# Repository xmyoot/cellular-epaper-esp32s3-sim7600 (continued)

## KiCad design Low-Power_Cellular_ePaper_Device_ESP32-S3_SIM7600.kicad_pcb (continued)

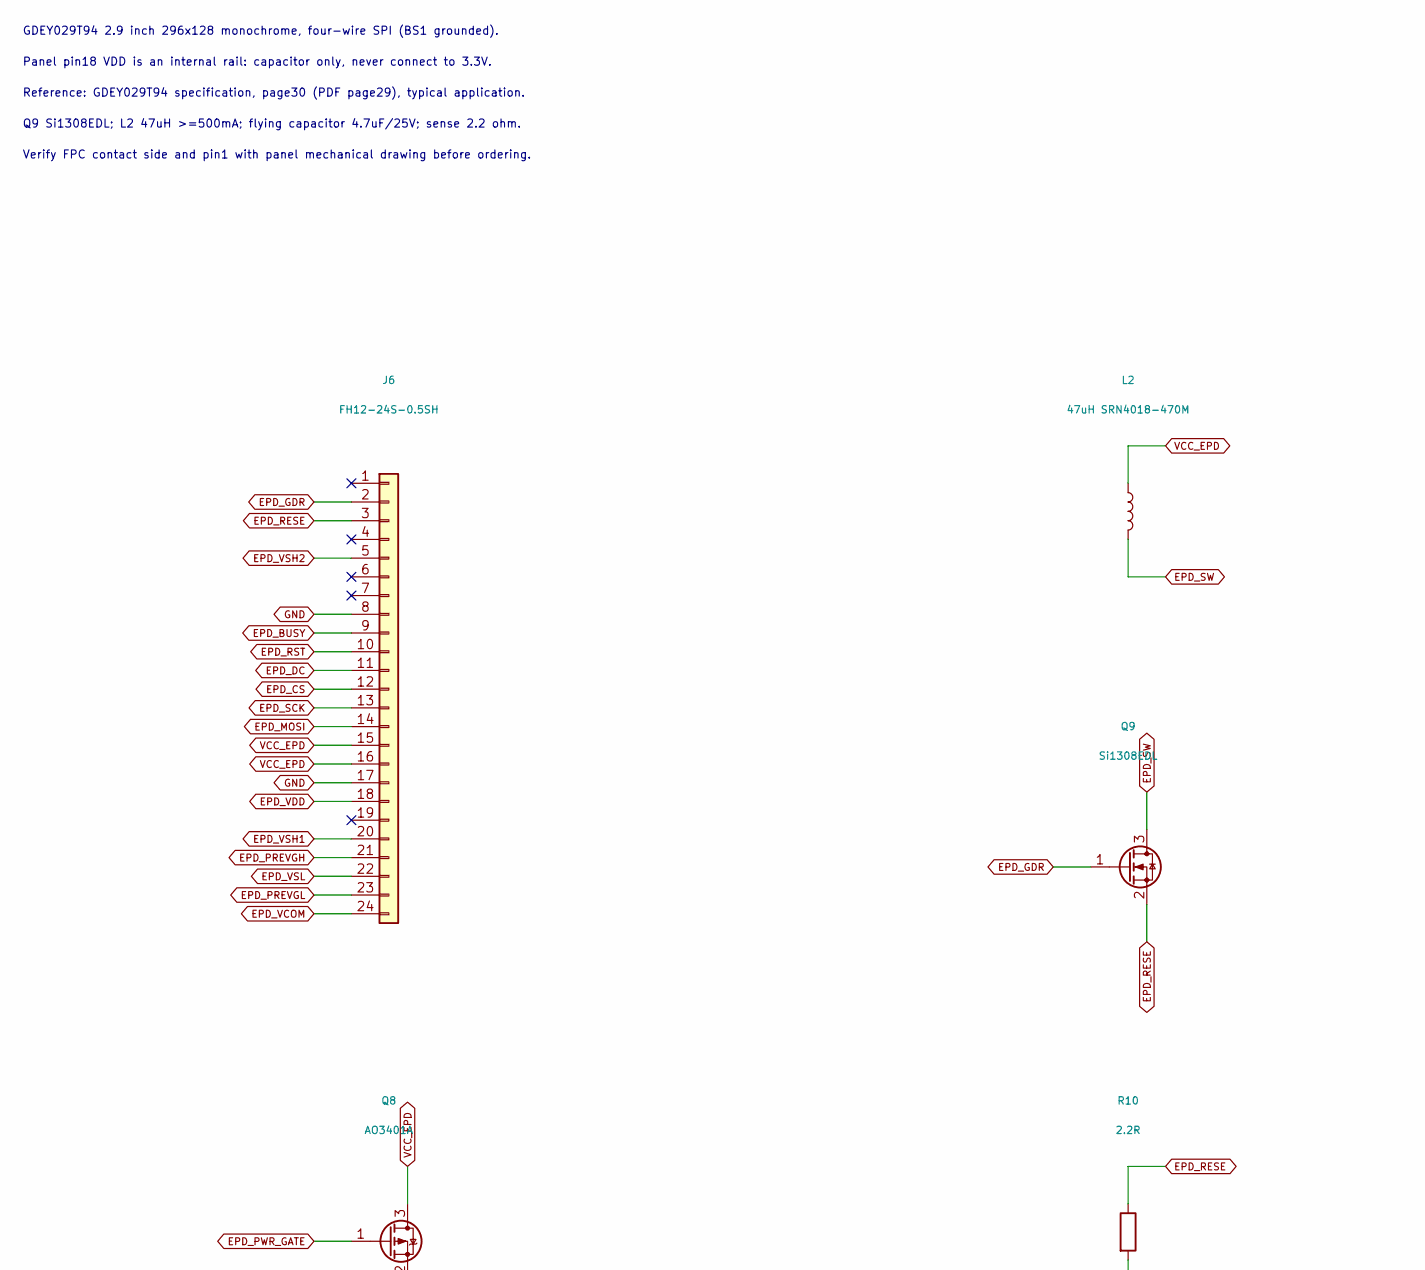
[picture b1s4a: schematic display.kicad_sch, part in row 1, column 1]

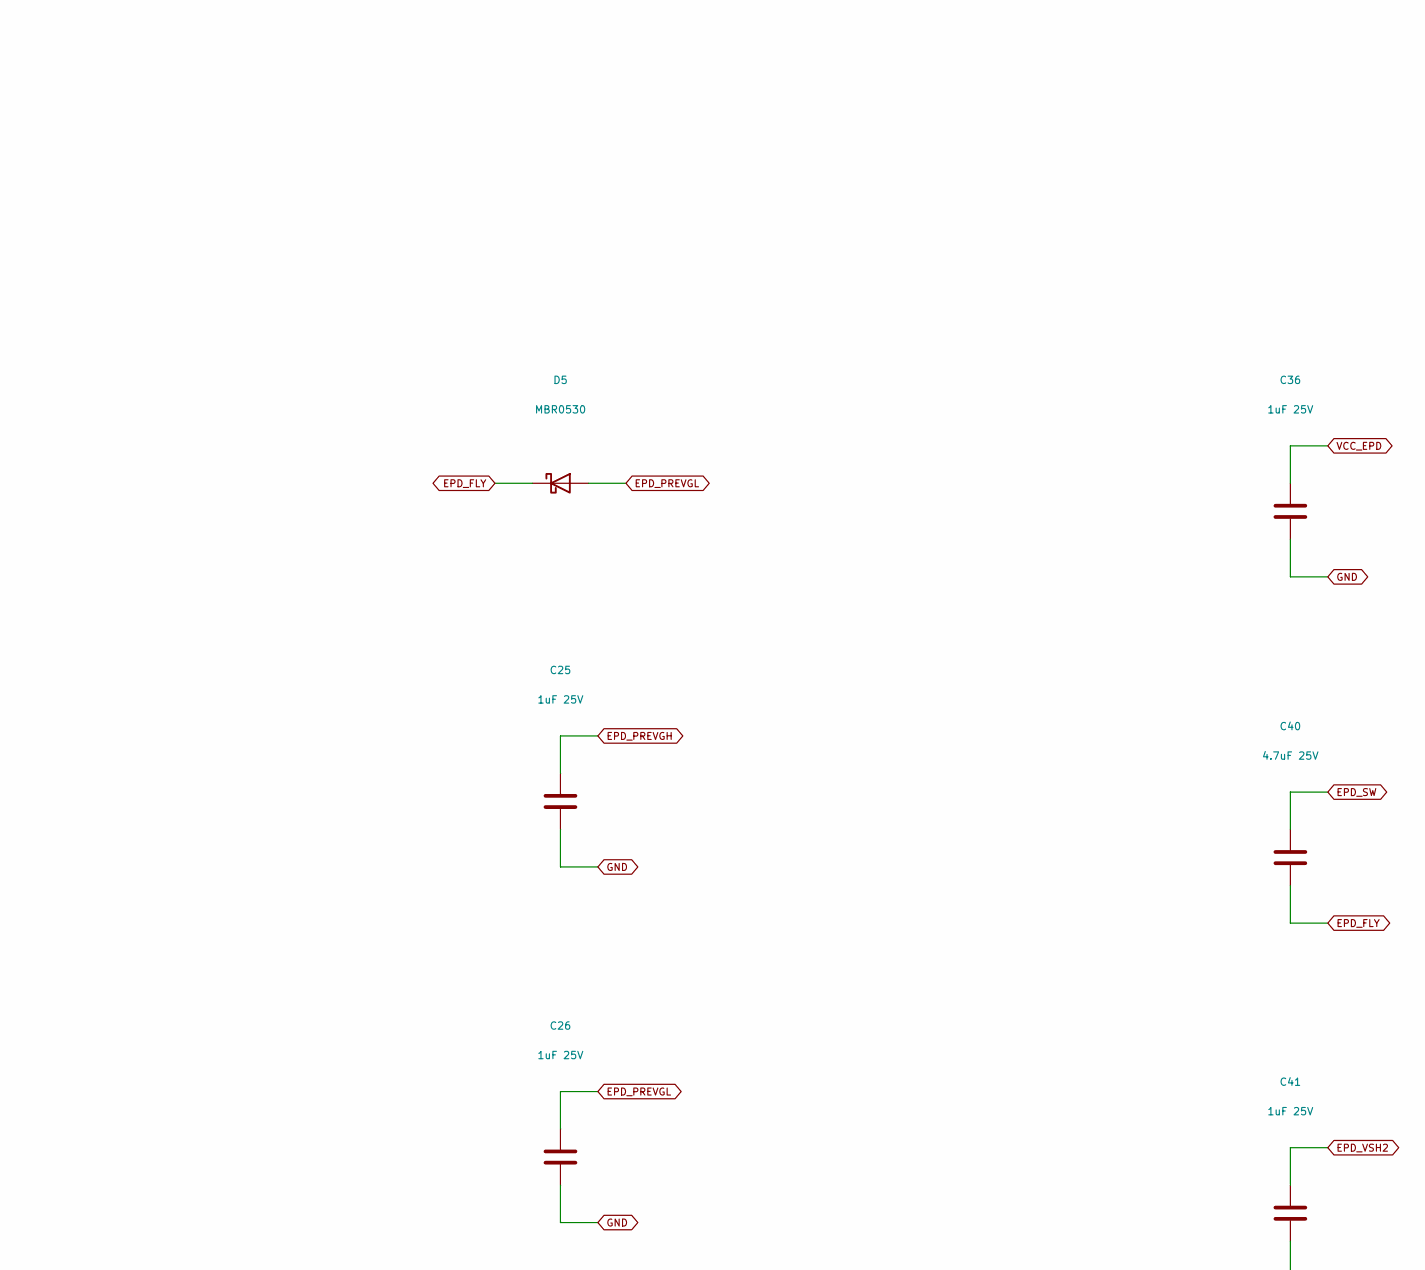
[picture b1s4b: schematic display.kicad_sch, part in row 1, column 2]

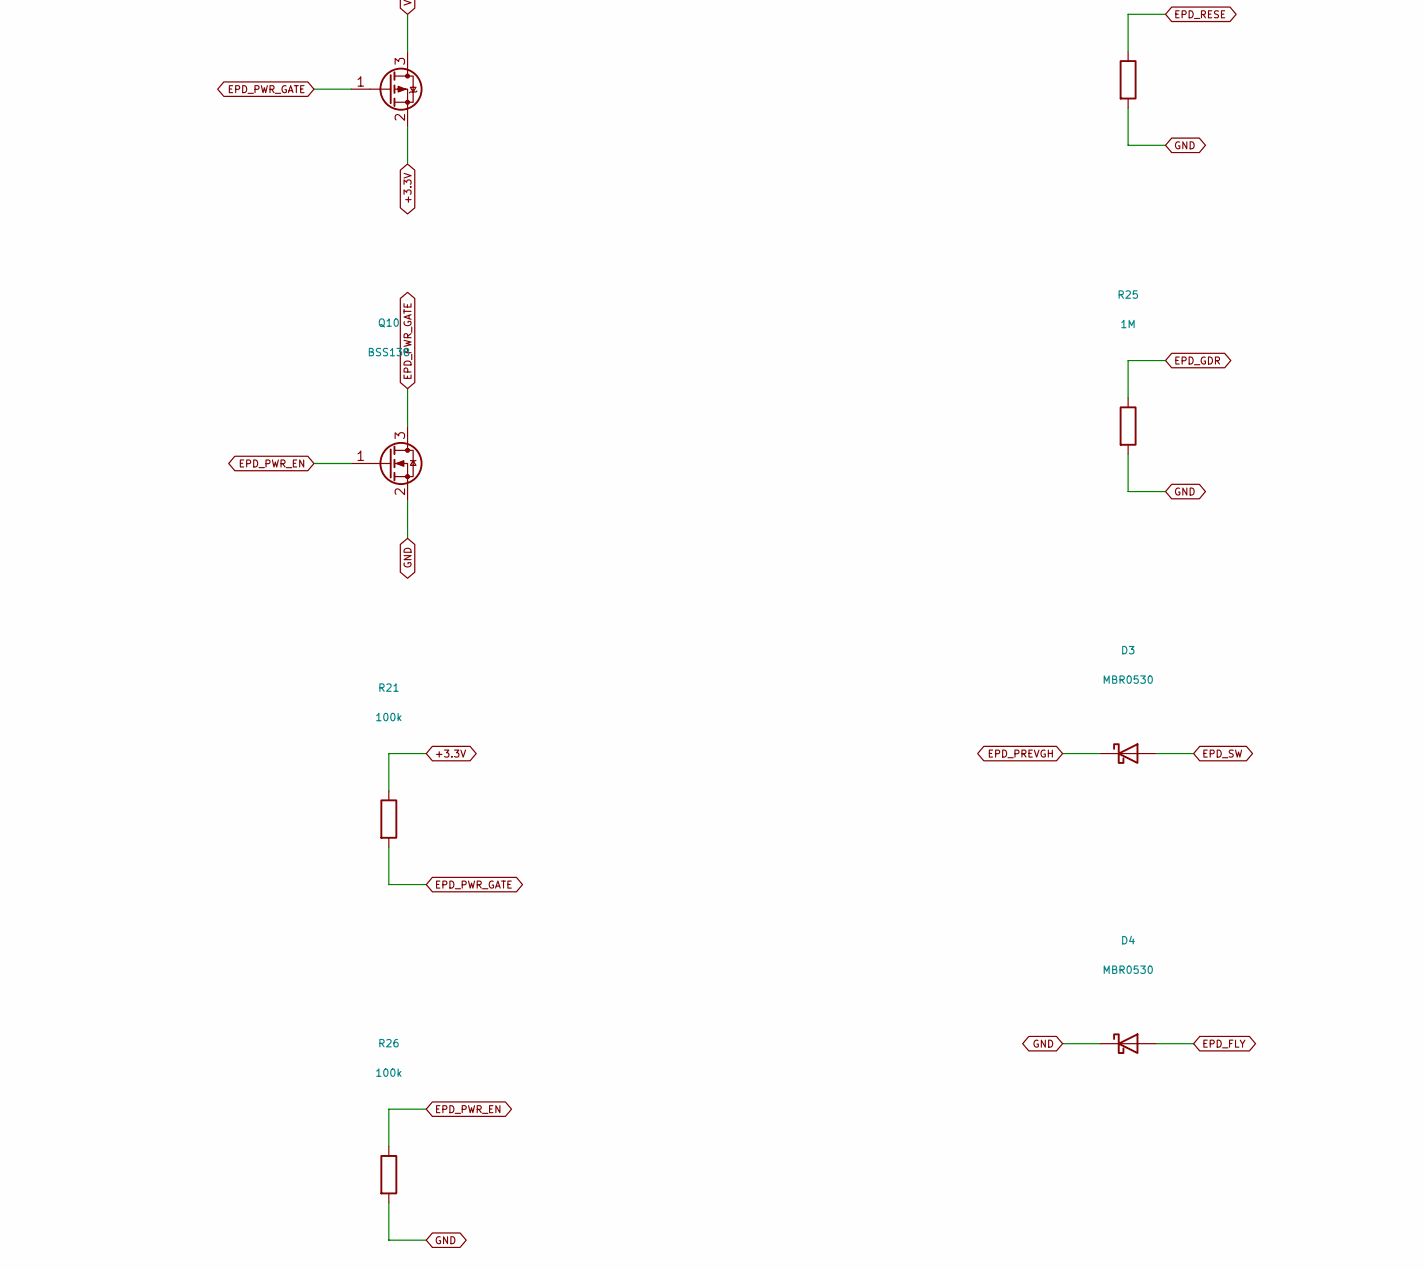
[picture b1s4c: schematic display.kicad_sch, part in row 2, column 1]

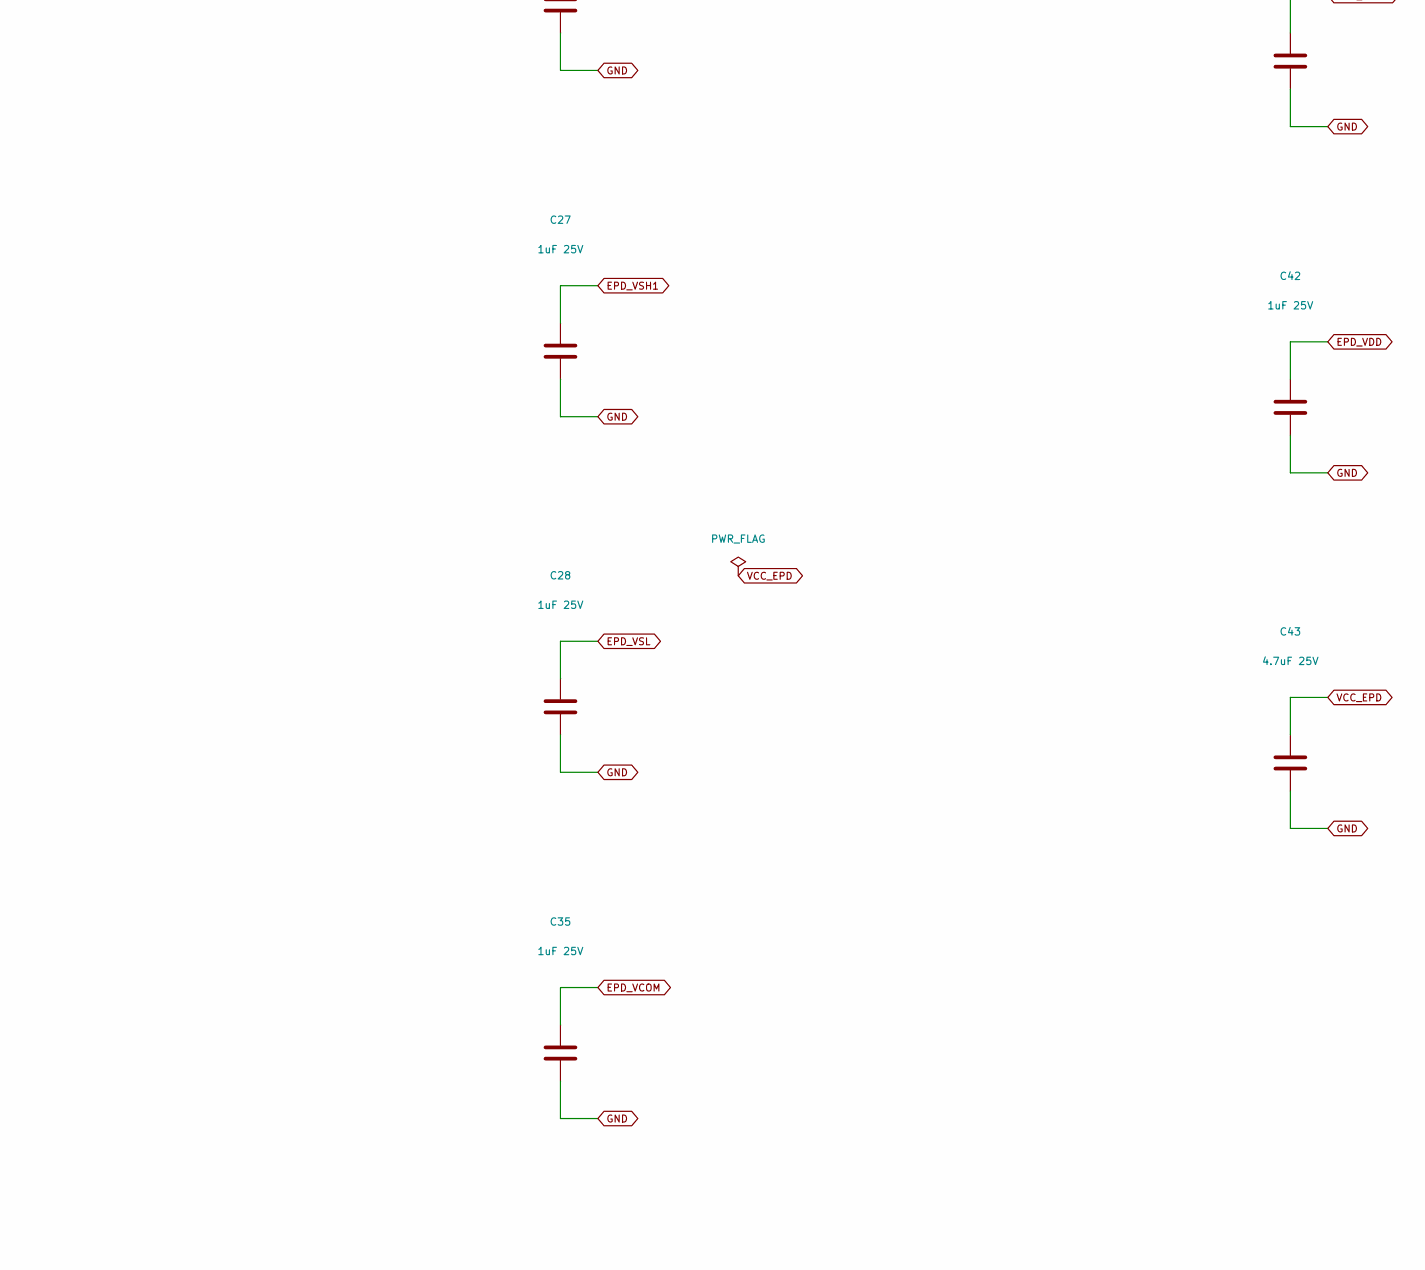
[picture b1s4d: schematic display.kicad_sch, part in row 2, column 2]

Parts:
C25, C26, C27, C28, C35, C41, C42: 1uF 25V; C_0805_2012Metric
C36: 1uF 25V; C_0603_1608Metric
C40, C43: 4.7uF 25V; C_0805_2012Metric
D3, D4, D5: MBR0530; D_SOD-123
J6: FH12-24S-0.5SH; Hirose_FH12-24S-0.5SH_1x24-1MP_P0.50mm_Horizontal
L2: 47uH SRN4018-470M; L_Bourns-SRN4018
Q8: AO3401A; SOT-23
Q9: Si1308EDL; SOT-323_SC-70
Q10: BSS138; SOT-23
R10: 2.2R; R_0805_2012Metric
R21, R26: 100k; R_0603_1608Metric
R25: 1M; R_0603_1608Metric

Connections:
+3.3V: Q8.2 (S), R21.1; also elsewhere on the board
EPD_BUSY: J6.9; also elsewhere on the board
EPD_CS: J6.12; also elsewhere on the board
EPD_DC: J6.11; also elsewhere on the board
EPD_FLY: C40.2, D4.2 (A), D5.1 (K)
EPD_GDR: J6.2, Q9.1 (G), R25.1
EPD_MOSI: J6.14; also elsewhere on the board
EPD_PREVGH: C25.1, D3.1 (K), J6.21
EPD_PREVGL: C26.1, D5.2 (A), J6.23
EPD_PWR_EN: Q10.1 (G), R26.1; also elsewhere on the board
EPD_PWR_GATE: Q8.1 (G), Q10.3 (D), R21.2
EPD_RESE: J6.3, Q9.2 (S), R10.1
EPD_RST: J6.10; also elsewhere on the board
EPD_SCK: J6.13; also elsewhere on the board
EPD_SW: C40.1, D3.2 (A), L2.2, Q9.3 (D)
EPD_VCOM: C35.1, J6.24
EPD_VDD: C42.1, J6.18
EPD_VSH1: C27.1, J6.20
EPD_VSH2: C41.1, J6.5
EPD_VSL: C28.1, J6.22
GND: C25.2, C26.2, C27.2, C28.2, C35.2, C36.2, C41.2, C42.2, C43.2, D4.1 (K), J6.8, J6.17, Q10.2 (S), R10.2, R25.2, R26.2; also elsewhere on the board
VCC_EPD: C36.1, C43.1, J6.15, J6.16, L2.1, Q8.3 (D)

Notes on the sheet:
Reference: GDEY029T94 specification, page30 (PDF page29), typical application.
Q9 Si1308EDL; L2 47uH >=500mA; flying capacitor 4.7uF/25V; sense 2.2 ohm.
Verify FPC contact side and pin1 with panel mechanical drawing before ordering.
GDEY029T94 2.9 inch 296x128 monochrome, four-wire SPI (BS1 grounded).
Panel pin18 VDD is an internal rail: capacitor only, never connect to 3.3V.

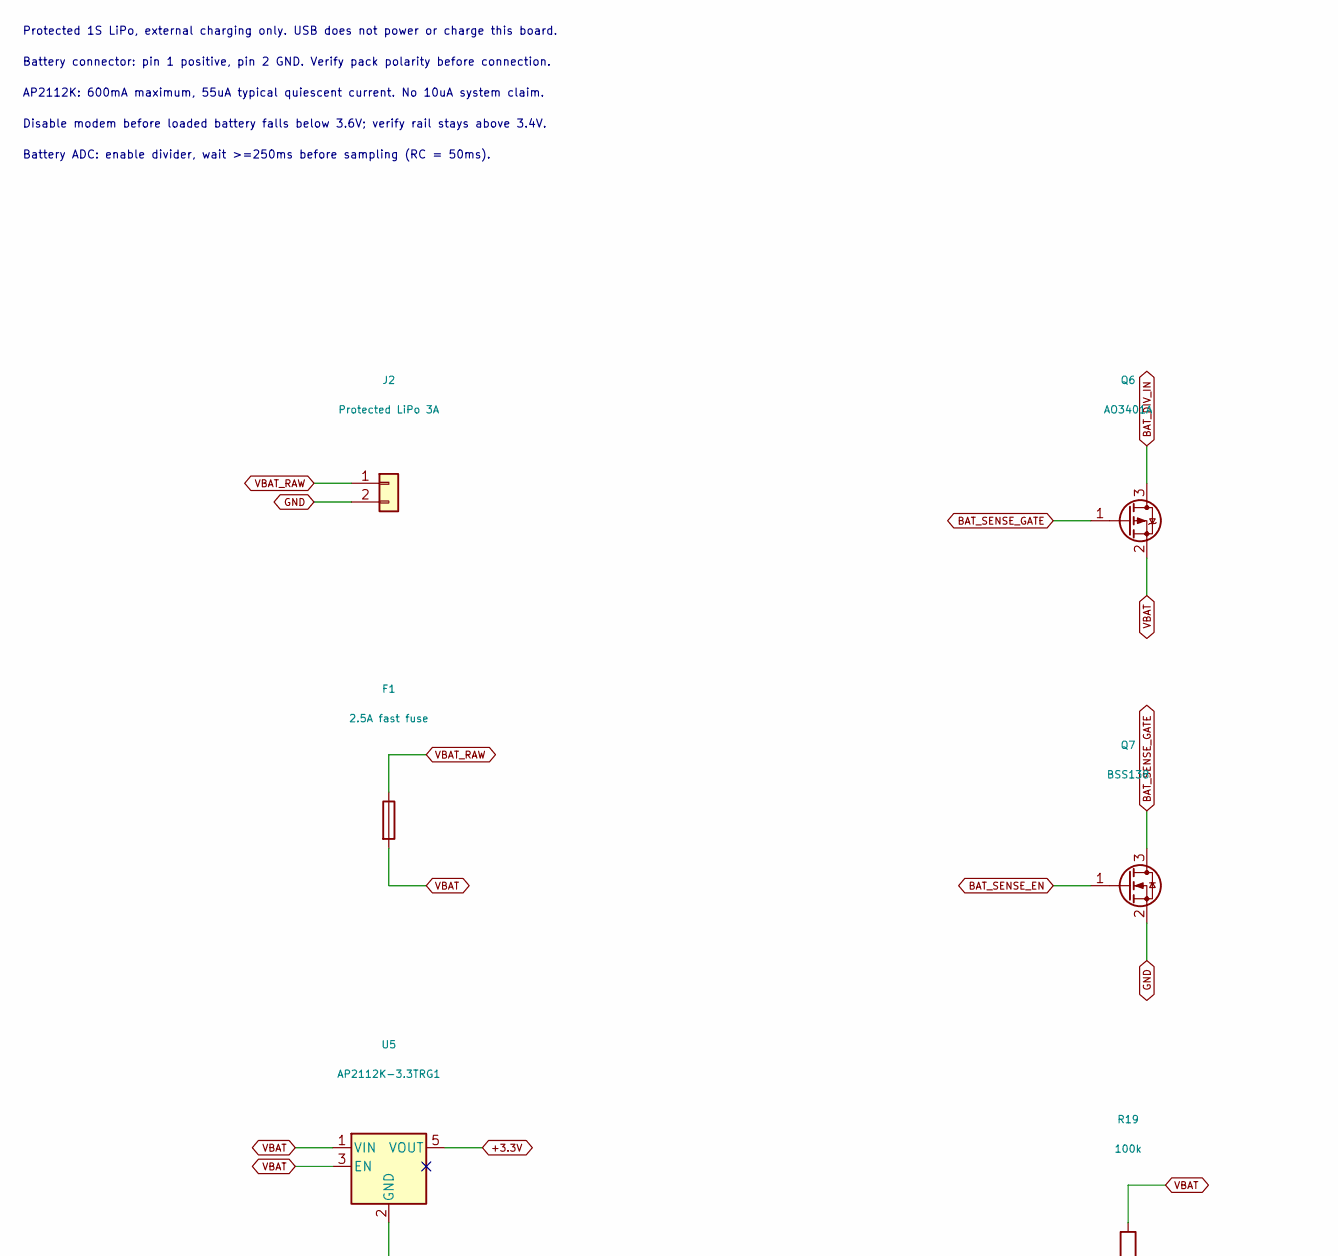
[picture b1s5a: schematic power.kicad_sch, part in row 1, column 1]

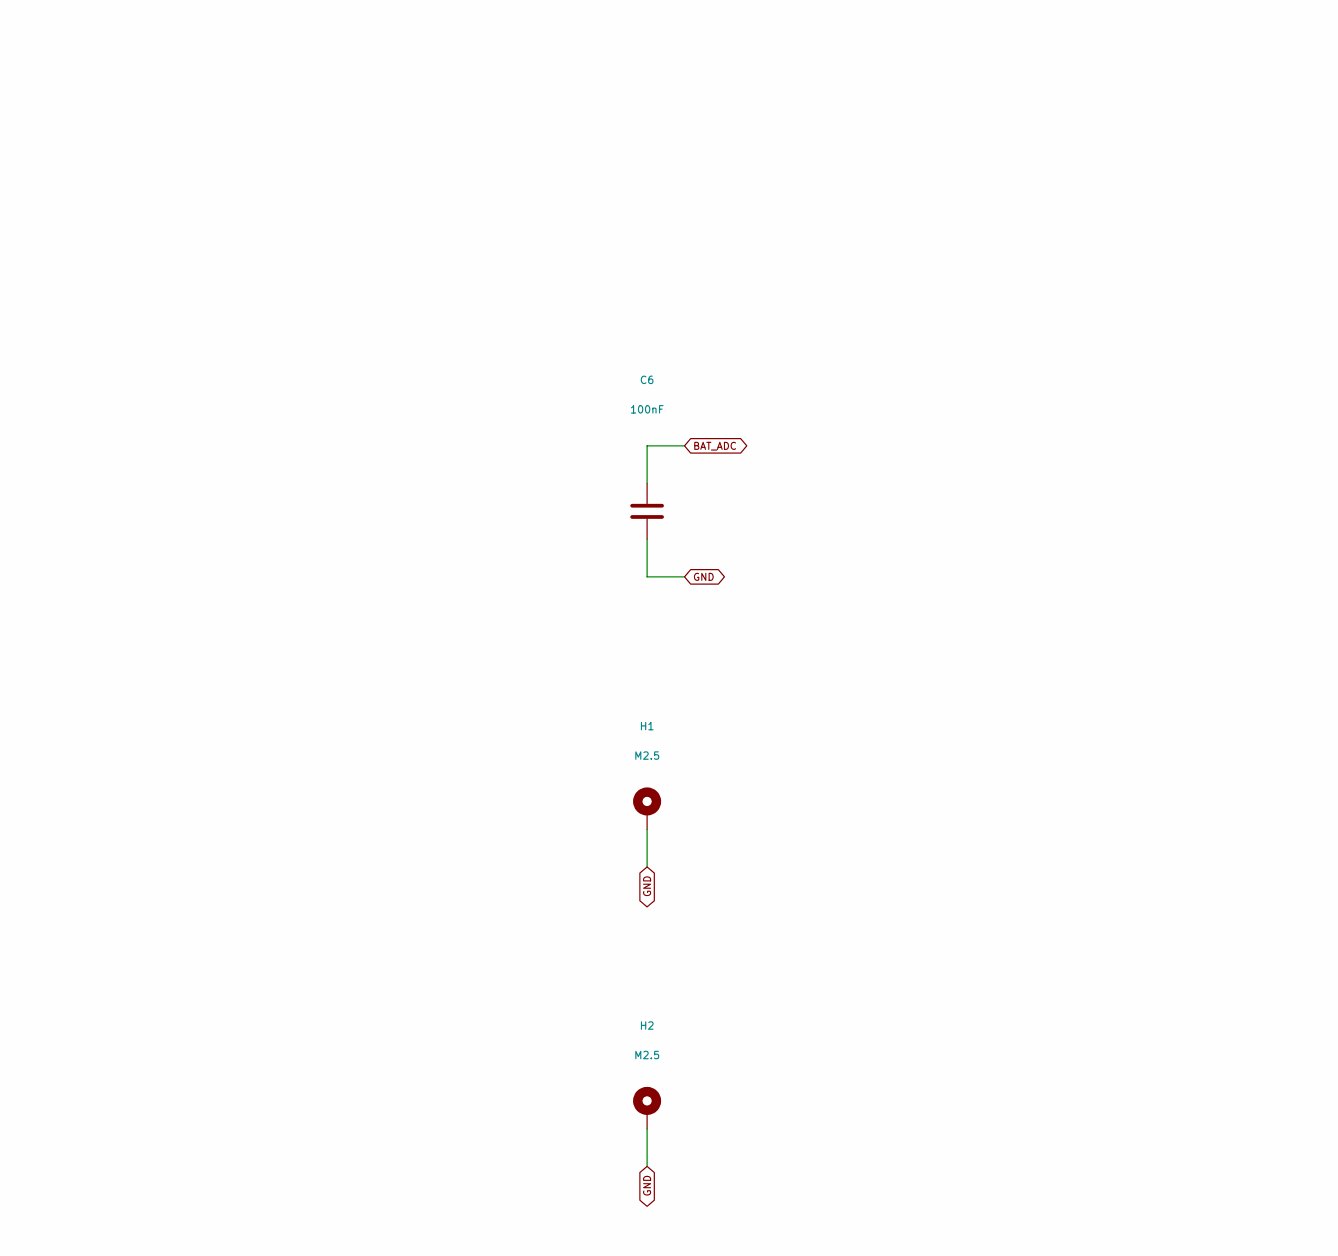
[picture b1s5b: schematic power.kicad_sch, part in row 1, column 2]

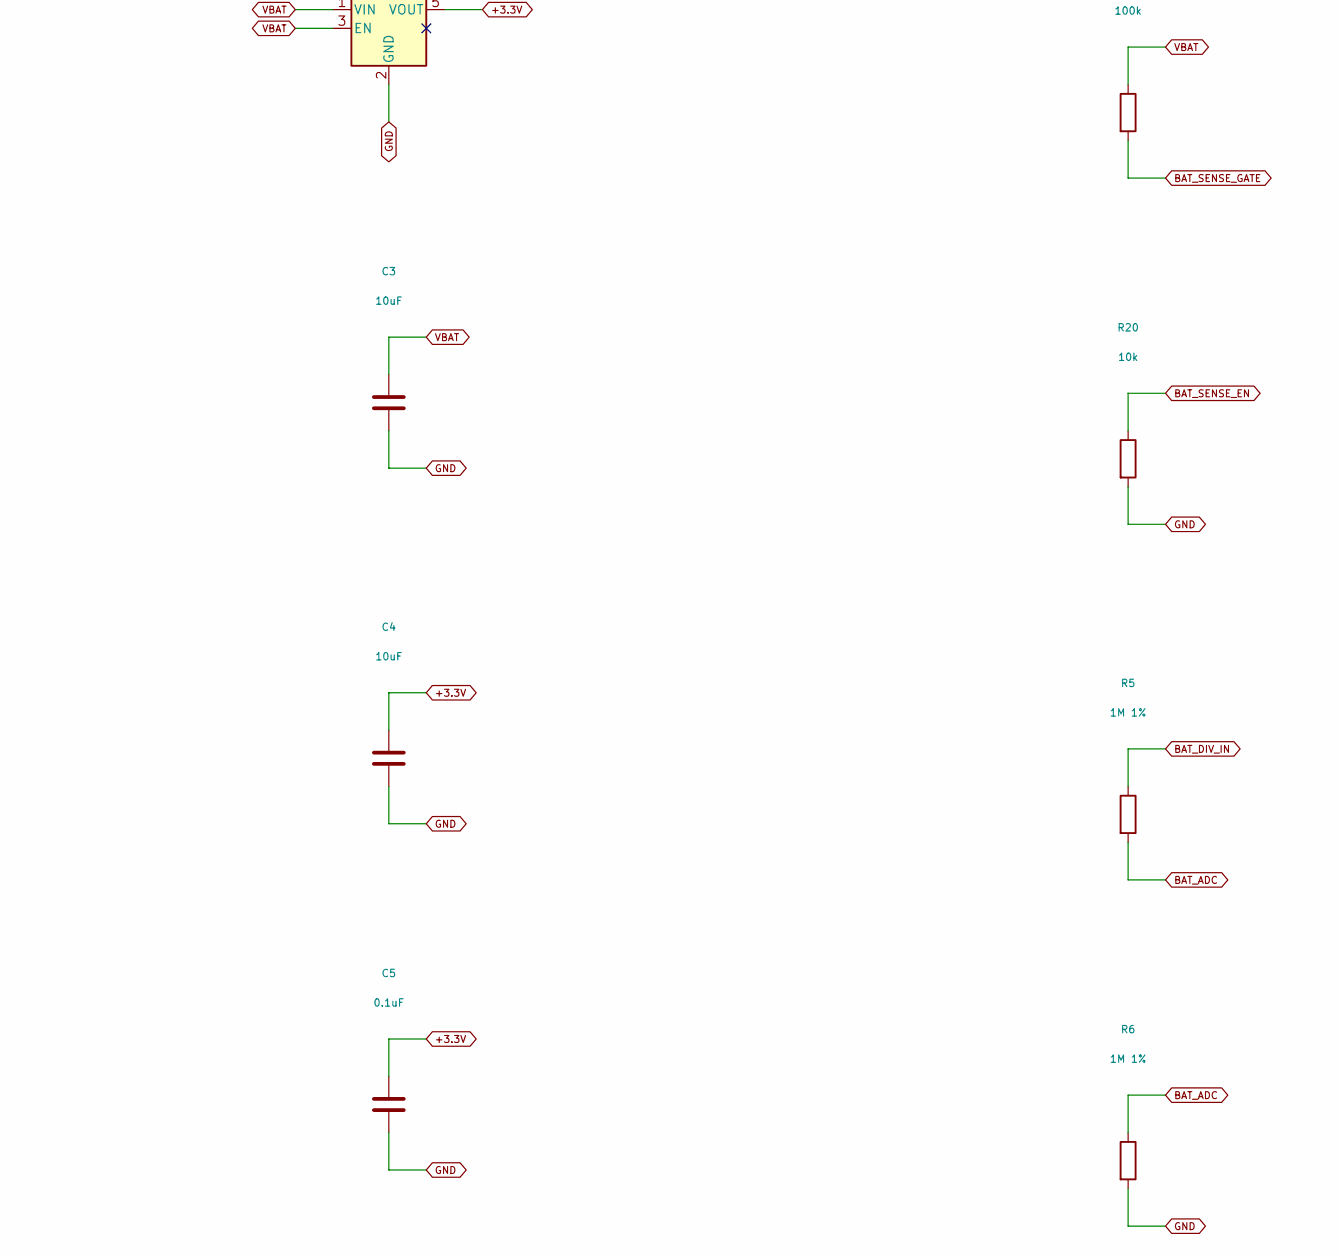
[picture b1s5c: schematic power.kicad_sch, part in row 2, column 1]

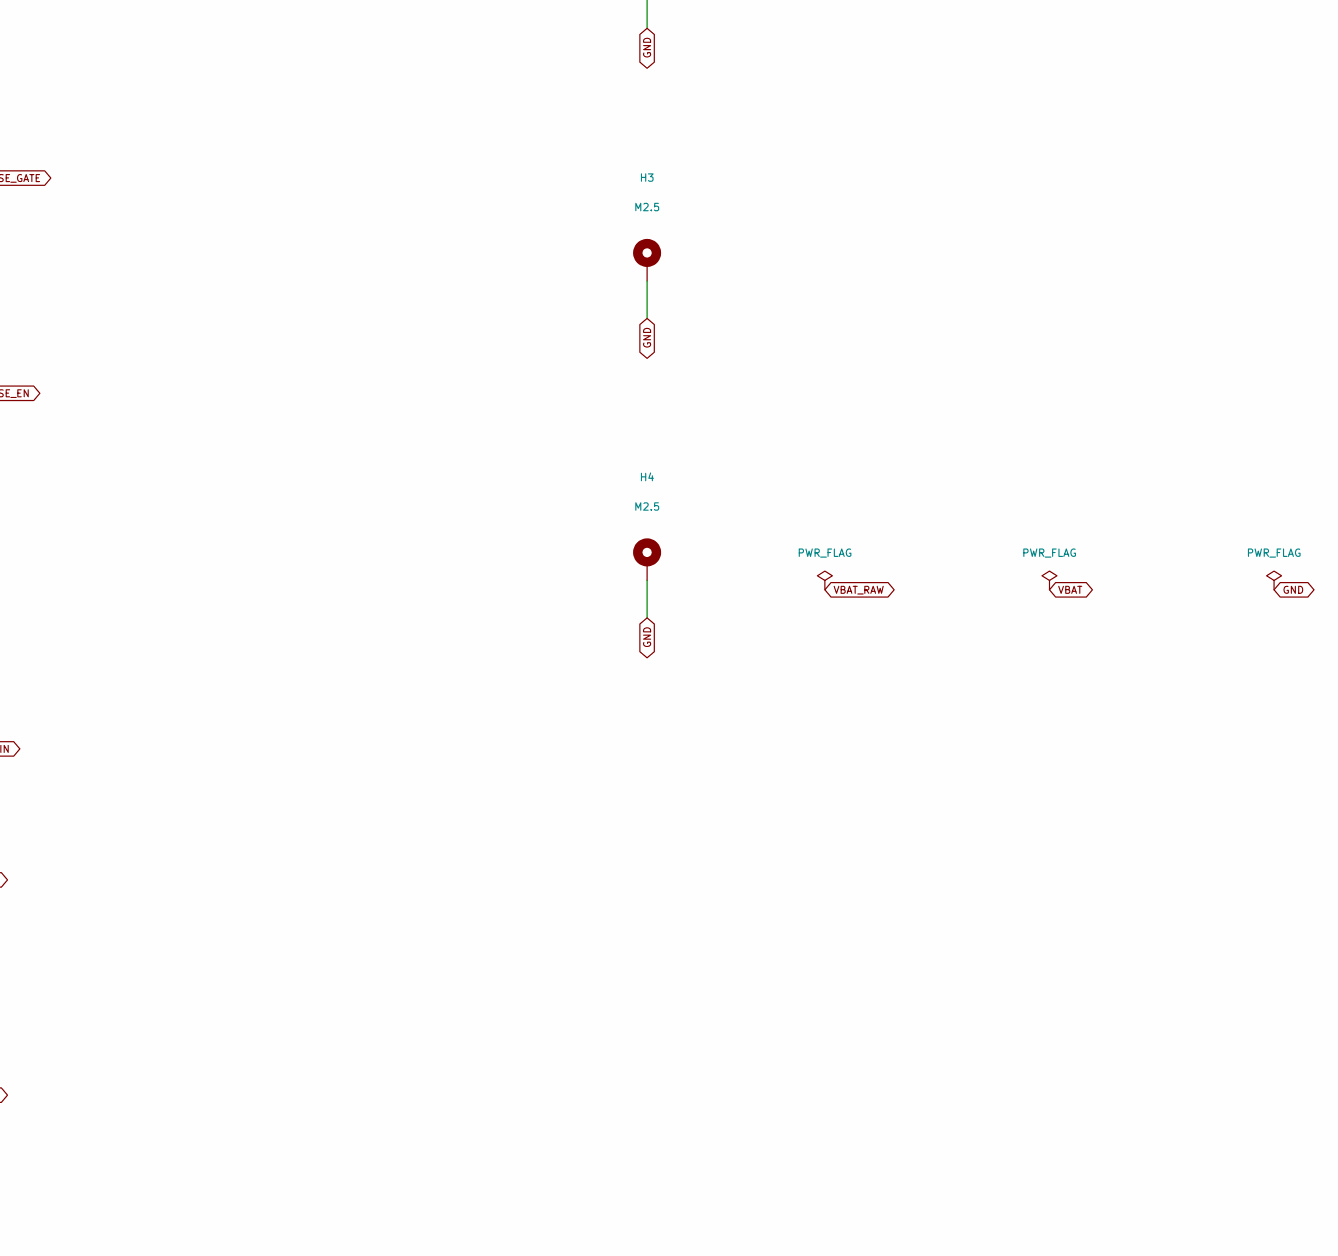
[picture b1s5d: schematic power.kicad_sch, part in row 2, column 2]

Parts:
C3, C4: 10uF; C_0805_2012Metric
C5: 0.1uF; C_0402_1005Metric
C6: 100nF; C_0402_1005Metric
F1: 2.5A fast fuse; Fuse_1206_3216Metric
H1, H2, H3, H4: M2.5; MountingHole_2.7mm_M2.5_Pad_Via
J2: Protected LiPo 3A; JST_XH_B2B-XH-A_1x02_P2.50mm_Vertical
Q6: AO3401A; SOT-23
Q7: BSS138; SOT-23
R5, R6: 1M 1%; R_0603_1608Metric
R19: 100k; R_0603_1608Metric
R20: 10k; R_0603_1608Metric
U5: AP2112K-3.3TRG1; SOT-23-5

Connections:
+3.3V: C4.1, C5.1, U5.5 (VOUT); also elsewhere on the board
BAT_ADC: C6.1, R5.2, R6.1; also elsewhere on the board
BAT_DIV_IN: Q6.3 (D), R5.1
BAT_SENSE_EN: Q7.1 (G), R20.1; also elsewhere on the board
BAT_SENSE_GATE: Q6.1 (G), Q7.3 (D), R19.2
GND: C3.2, C4.2, C5.2, C6.2, H1.1 (1_1), H2.1 (1_1), H3.1 (1_1), H4.1 (1_1), J2.2, Q7.2 (S), R6.2, R20.2, U5.2 (GND); also elsewhere on the board
VBAT: C3.1, F1.2, Q6.2 (S), R19.1, U5.1 (VIN), U5.3 (EN); also elsewhere on the board
VBAT_RAW: F1.1, J2.1

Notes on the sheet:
AP2112K: 600mA maximum, 55uA typical quiescent current. No 10uA system claim.
Protected 1S LiPo, external charging only. USB does not power or charge this board.
Battery ADC: enable divider, wait >=250ms before sampling (RC = 50ms).
Battery connector: pin 1 positive, pin 2 GND. Verify pack polarity before connection.
Disable modem before loaded battery falls below 3.6V; verify rail stays above 3.4V.

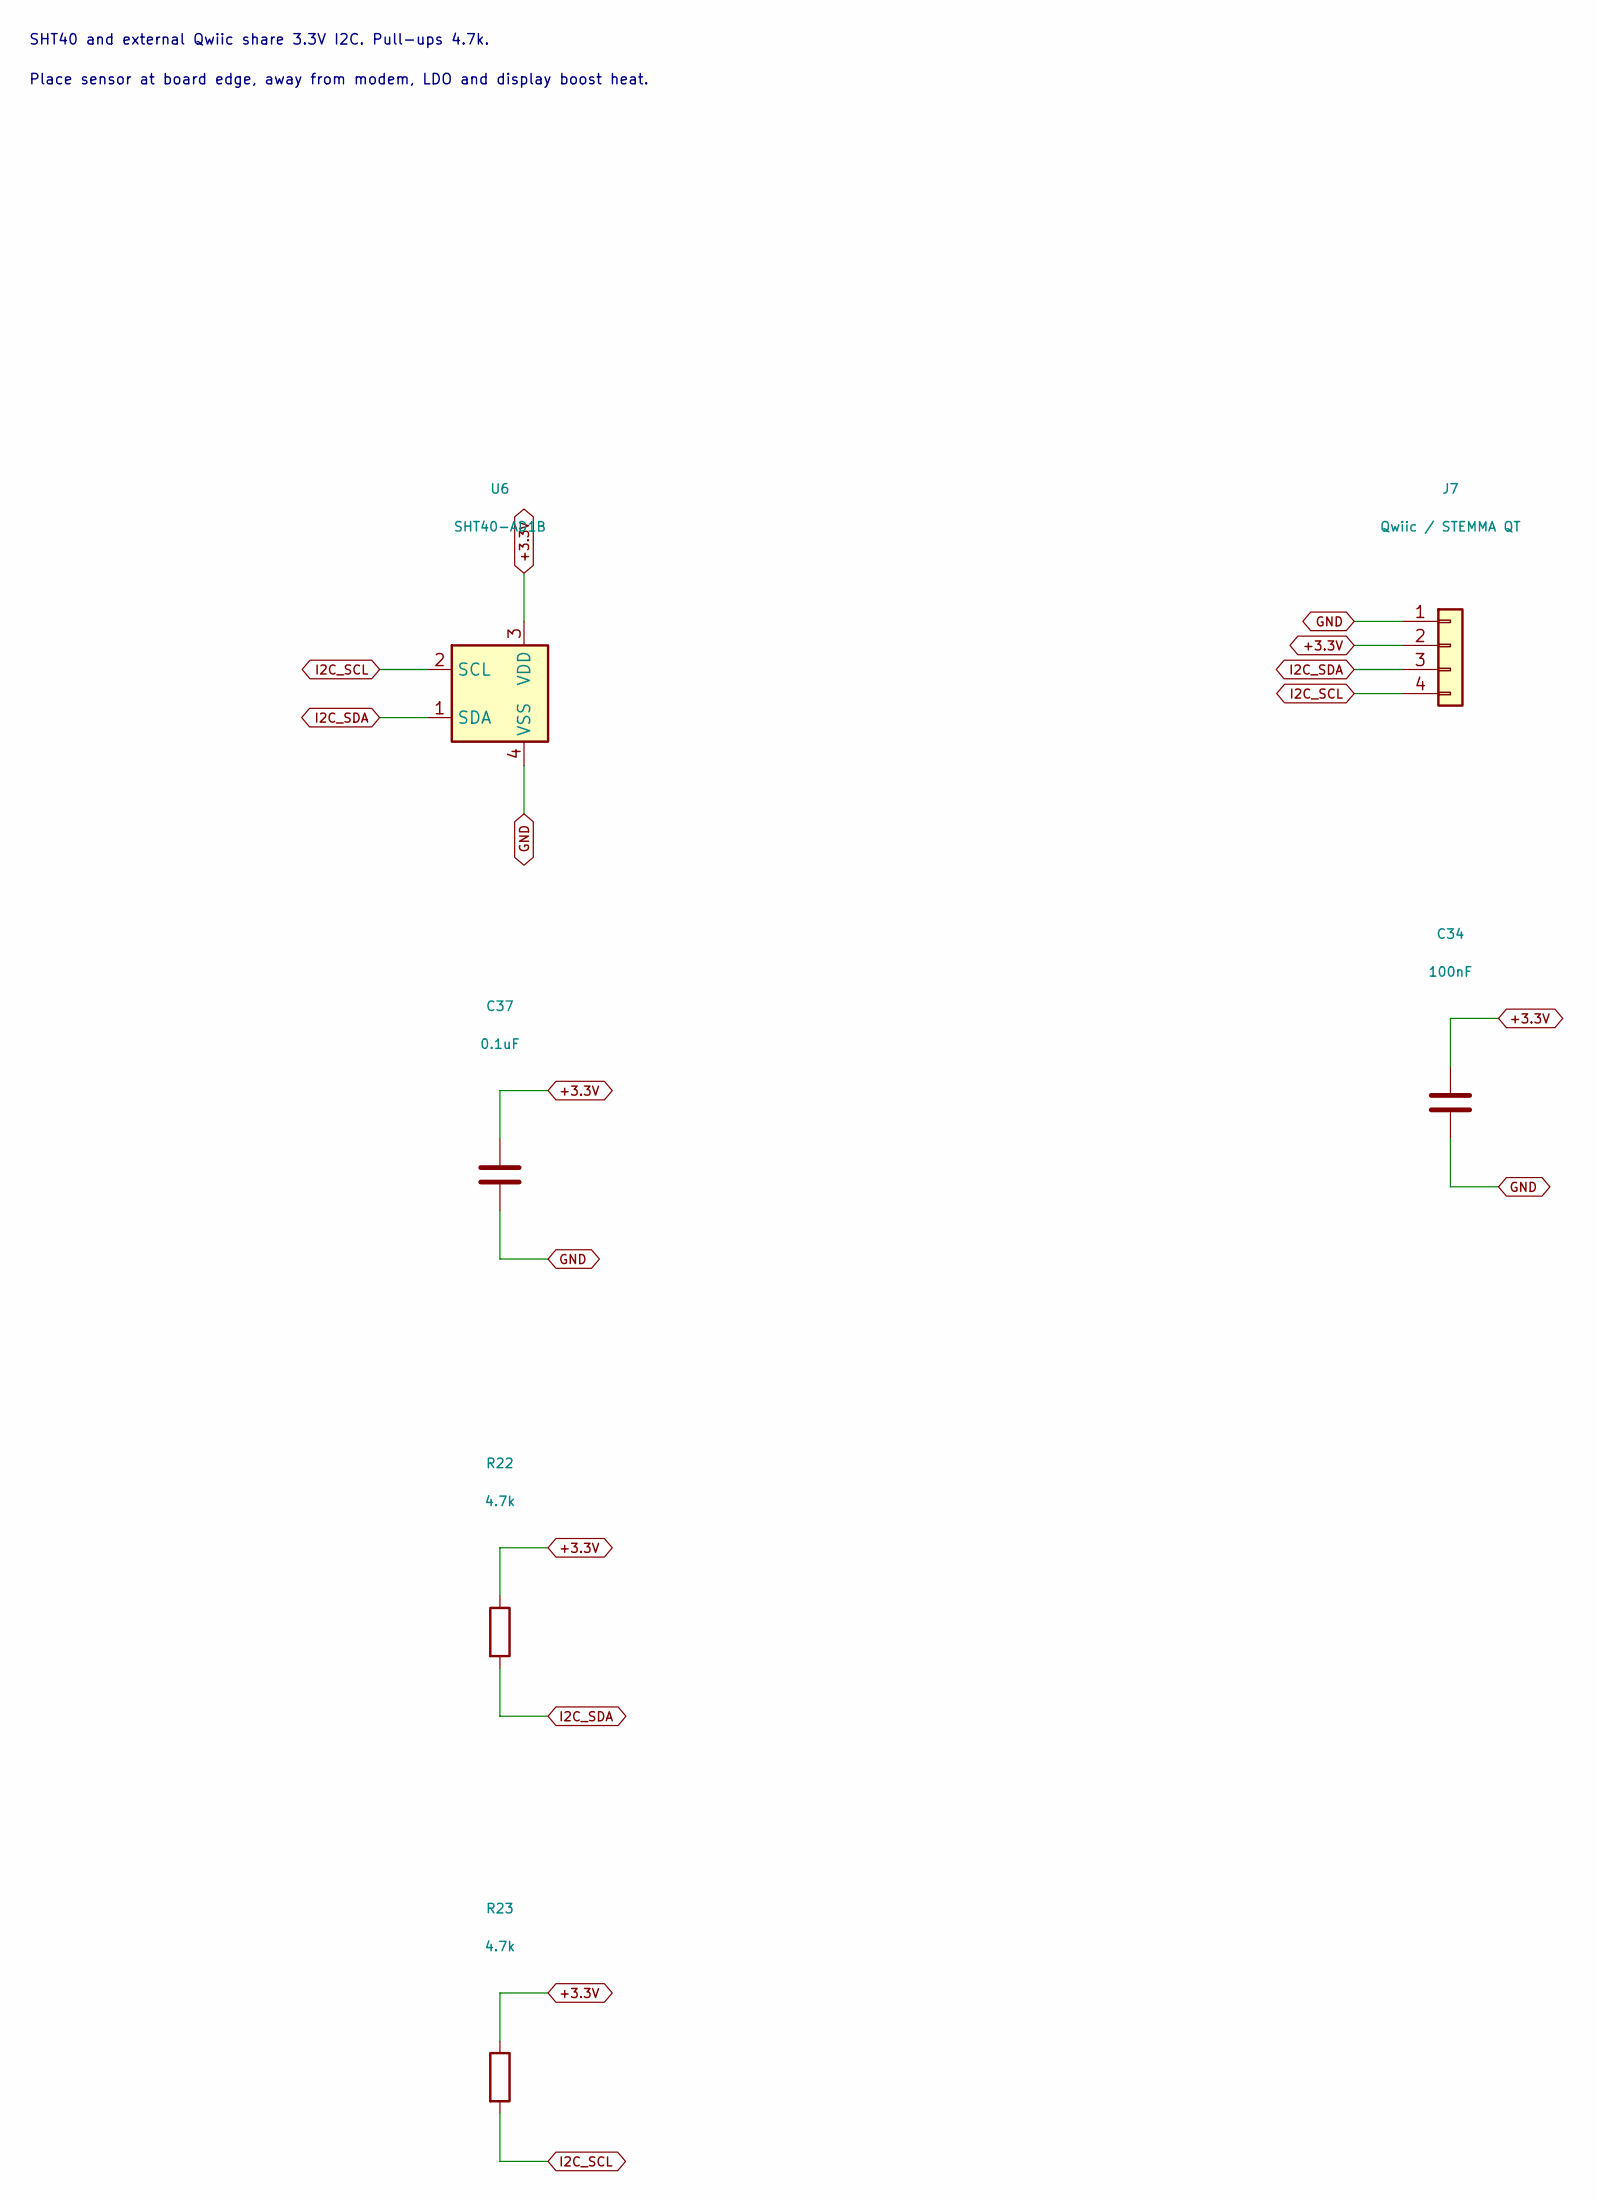
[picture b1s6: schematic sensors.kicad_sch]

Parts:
C34: 100nF; C_0402_1005Metric
C37: 0.1uF; C_0402_1005Metric
J7: Qwiic / STEMMA QT; JST_SH_SM04B-SRSS-TB_1x04-1MP_P1.00mm_Horizontal
R22, R23: 4.7k; R_0603_1608Metric
U6: SHT40-AD1B; Sensirion_DFN-4_1.5x1.5mm_P0.8mm_SHT4x_NoCentralPad

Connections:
+3.3V: C34.1, C37.1, J7.2, R22.1, R23.1, U6.3 (VDD); also elsewhere on the board
GND: C34.2, C37.2, J7.1, U6.4 (VSS); also elsewhere on the board
I2C_SCL: J7.4, R23.2, U6.2 (SCL); also elsewhere on the board
I2C_SDA: J7.3, R22.2, U6.1 (SDA); also elsewhere on the board

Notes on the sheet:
Place sensor at board edge, away from modem, LDO and display boost heat.
SHT40 and external Qwiic share 3.3V I2C. Pull-ups 4.7k.
